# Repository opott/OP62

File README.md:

# OP62
This is a 60% (62 key) mechanical keyboard designed for Hackpad V2.

## PCB

## Case
The 3D printed case will consist of three parts:
- Top Assembly
- Plate
- Bottom Assembly

The top and bottom assembly will be attached with magnets. This is a screwless keyboard!

## Firmware
The current firmware is a **VERY** basic prototype created with [Pog](https://pog.heaper.de/).

A final firmware version will be created upon recieving the hardware.

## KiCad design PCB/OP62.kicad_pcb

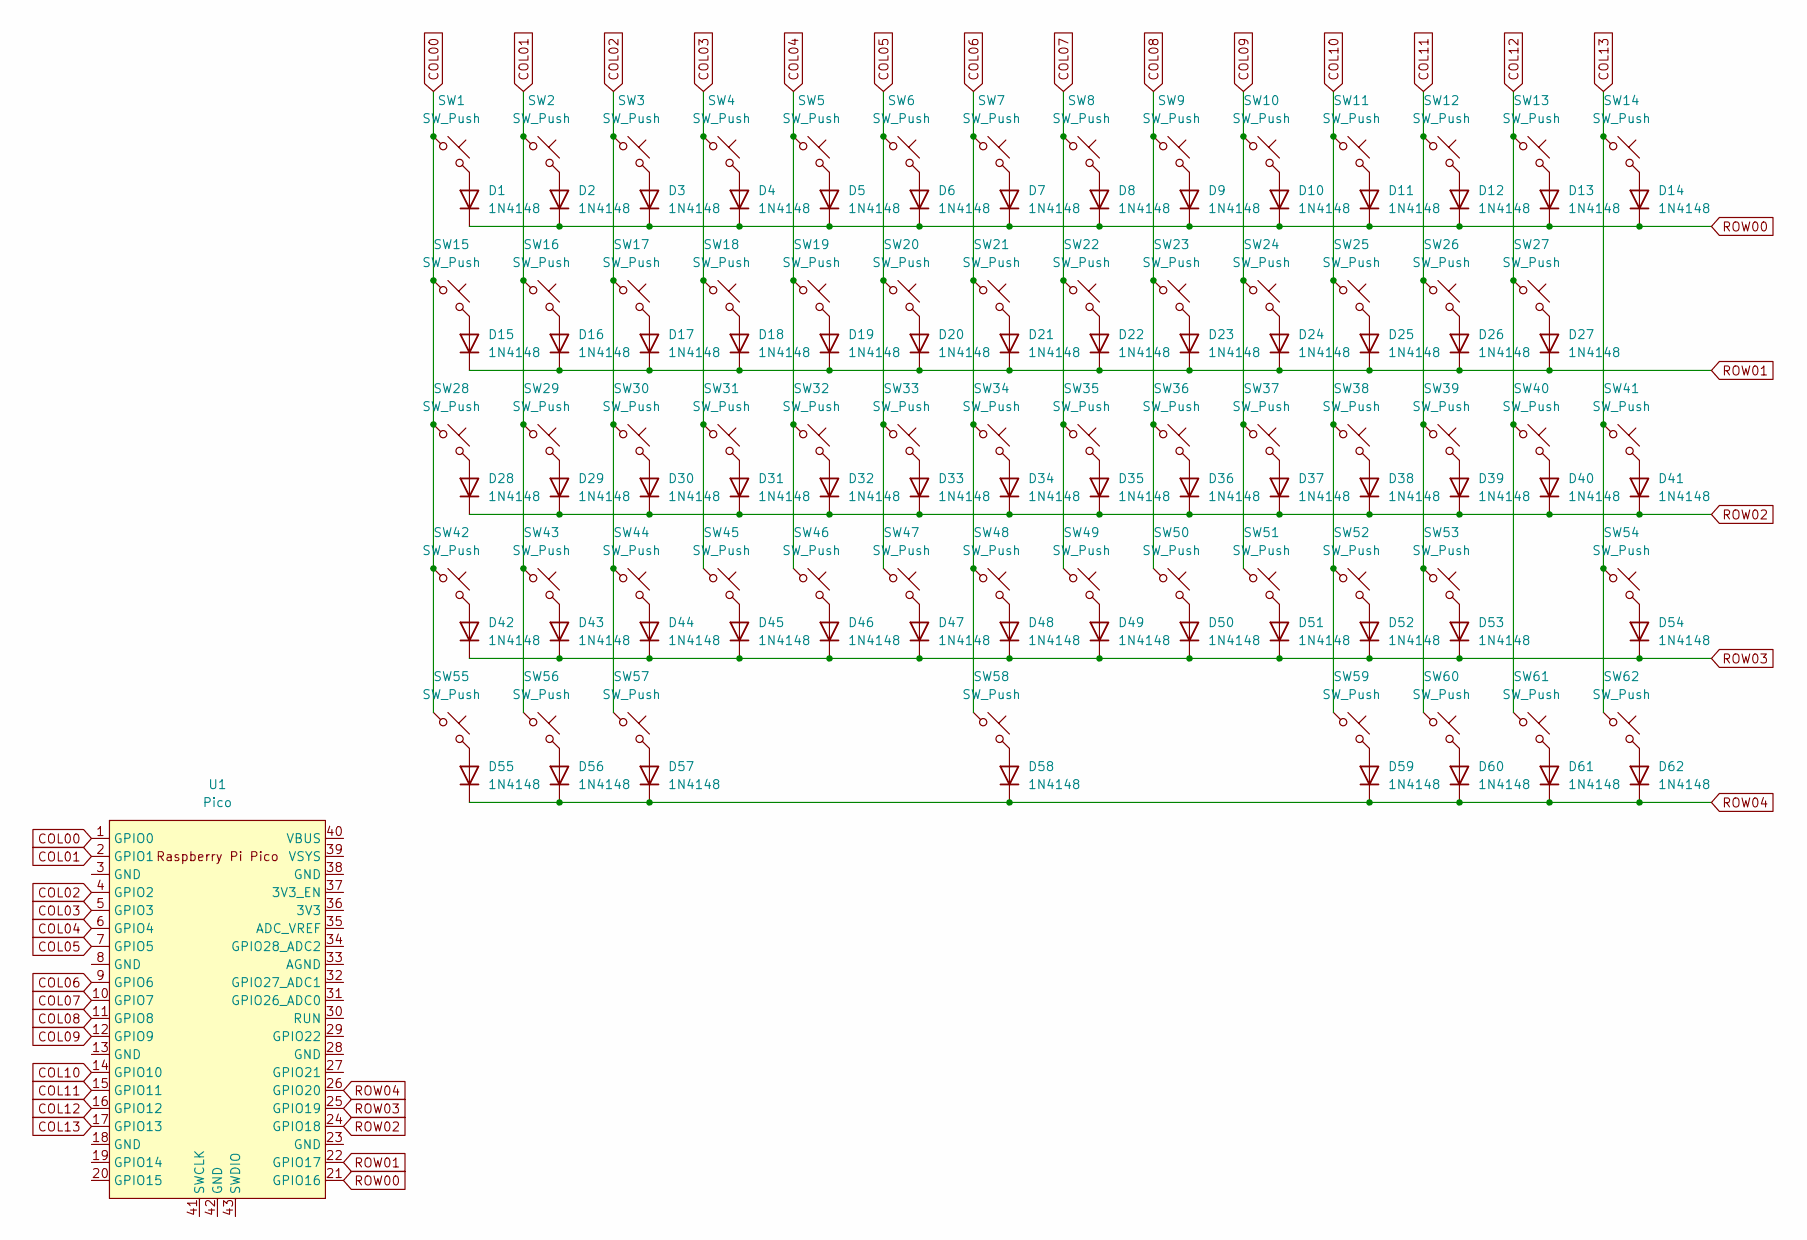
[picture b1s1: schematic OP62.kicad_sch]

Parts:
D1, D2, D3, D4, D5, D6, D7, D8, D9, D10, D11, D12, D13, D14, D15, D16, D17, D18, D19, D20, D21, D22, D23, D24, D25, D26, D27, D28, D29, D30, D31, D32, D33, D34, D35, D36, D37, D38, D39, D40, D41, D42, D43, D44, D45, D46, D47, D48, D49, D50, D51, D52, D53, D54, D55, D56, D57, D58, D59, D60, D61, D62: 1N4148; D_DO-35_SOD27_P7.62mm_Horizontal
SW1, SW2, SW3, SW4, SW5, SW6, SW7, SW8, SW9, SW10, SW11, SW12, SW13, SW16, SW17, SW18, SW19, SW20, SW21, SW22, SW23, SW24, SW25, SW26, SW27, SW29, SW30, SW31, SW32, SW33, SW34, SW35, SW36, SW37, SW38, SW39, SW40, SW43, SW44, SW45, SW46, SW47, SW48, SW49, SW50, SW51, SW52, SW53: SW_Push; MX-Alps-Hybrid-1U
SW14: SW_Push; MX-Alps-Hybrid-2U
SW15: SW_Push; MX-Alps-Hybrid-1.5U
SW28: SW_Push; MX-Alps-Hybrid-1.75U
SW41: SW_Push; MX-Alps-Hybrid-ISO
SW42, SW55, SW56, SW57, SW59, SW60, SW61, SW62: SW_Push; MX-Alps-Hybrid-1.25U
SW54: SW_Push; MX-Alps-Hybrid-2.75U
SW58: SW_Push; MX-Alps-Hybrid-6.25U
U1: Pico; RPi_Pico_SMD_TH

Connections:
COL00: SW1.1, SW15.1, SW28.1, SW42.1, SW55.1, U1.1 (GPIO0)
COL01: SW2.1, SW16.1, SW29.1, SW43.1, SW56.1, U1.2 (GPIO1)
COL02: SW3.1, SW17.1, SW30.1, SW44.1, SW57.1, U1.4 (GPIO2)
COL03: SW4.1, SW18.1, SW31.1, SW45.1, U1.5 (GPIO3)
COL04: SW5.1, SW19.1, SW32.1, SW46.1, U1.6 (GPIO4)
COL05: SW6.1, SW20.1, SW33.1, SW47.1, U1.7 (GPIO5)
COL06: SW7.1, SW21.1, SW34.1, SW48.1, SW58.1, U1.9 (GPIO6)
COL07: SW8.1, SW22.1, SW35.1, SW49.1, U1.10 (GPIO7)
COL08: SW9.1, SW23.1, SW36.1, SW50.1, U1.11 (GPIO8)
COL09: SW10.1, SW24.1, SW37.1, SW51.1, U1.12 (GPIO9)
COL10: SW11.1, SW25.1, SW38.1, SW52.1, SW59.1, U1.14 (GPIO10)
COL11: SW12.1, SW26.1, SW39.1, SW53.1, SW60.1, U1.15 (GPIO11)
COL12: SW13.1, SW27.1, SW40.1, SW61.1, U1.16 (GPIO12)
COL13: SW14.1, SW41.1, SW54.1, SW62.1, U1.17 (GPIO13)
unnamed: D1.2 (A), SW1.2
unnamed: D2.2 (A), SW2.2
unnamed: D3.2 (A), SW3.2
unnamed: D4.2 (A), SW4.2
unnamed: D5.2 (A), SW5.2
unnamed: D6.2 (A), SW6.2
unnamed: D7.2 (A), SW7.2
unnamed: D8.2 (A), SW8.2
unnamed: D9.2 (A), SW9.2
unnamed: D10.2 (A), SW10.2
unnamed: D11.2 (A), SW11.2
unnamed: D12.2 (A), SW12.2
unnamed: D13.2 (A), SW13.2
unnamed: D14.2 (A), SW14.2
unnamed: D15.2 (A), SW15.2
unnamed: D16.2 (A), SW16.2
unnamed: D17.2 (A), SW17.2
unnamed: D18.2 (A), SW18.2
unnamed: D19.2 (A), SW19.2
unnamed: D20.2 (A), SW20.2
unnamed: D21.2 (A), SW21.2
unnamed: D22.2 (A), SW22.2
unnamed: D23.2 (A), SW23.2
unnamed: D24.2 (A), SW24.2
unnamed: D25.2 (A), SW25.2
unnamed: D26.2 (A), SW26.2
unnamed: D27.2 (A), SW27.2
unnamed: D28.2 (A), SW28.2
unnamed: D29.2 (A), SW29.2
unnamed: D30.2 (A), SW30.2
unnamed: D31.2 (A), SW31.2
unnamed: D32.2 (A), SW32.2
unnamed: D33.2 (A), SW33.2
unnamed: D34.2 (A), SW34.2
unnamed: D35.2 (A), SW35.2
unnamed: D36.2 (A), SW36.2
unnamed: D37.2 (A), SW37.2
unnamed: D38.2 (A), SW38.2
unnamed: D39.2 (A), SW39.2
unnamed: D40.2 (A), SW40.2
unnamed: D41.2 (A), SW41.2
unnamed: D42.2 (A), SW42.2
unnamed: D43.2 (A), SW43.2
unnamed: D44.2 (A), SW44.2
unnamed: D45.2 (A), SW45.2
unnamed: D46.2 (A), SW46.2
unnamed: D47.2 (A), SW47.2
unnamed: D48.2 (A), SW48.2
unnamed: D49.2 (A), SW49.2
unnamed: D50.2 (A), SW50.2
unnamed: D51.2 (A), SW51.2
unnamed: D52.2 (A), SW52.2
unnamed: D53.2 (A), SW53.2
unnamed: D54.2 (A), SW54.2
unnamed: D55.2 (A), SW55.2
unnamed: D56.2 (A), SW56.2
unnamed: D57.2 (A), SW57.2
unnamed: D58.2 (A), SW58.2
unnamed: D59.2 (A), SW59.2
unnamed: D60.2 (A), SW60.2
unnamed: D61.2 (A), SW61.2
unnamed: D62.2 (A), SW62.2
ROW00: D1.1 (K), D2.1 (K), D3.1 (K), D4.1 (K), D5.1 (K), D6.1 (K), D7.1 (K), D8.1 (K), D9.1 (K), D10.1 (K), D11.1 (K), D12.1 (K), D13.1 (K), D14.1 (K), U1.21 (GPIO16)
ROW01: D15.1 (K), D16.1 (K), D17.1 (K), D18.1 (K), D19.1 (K), D20.1 (K), D21.1 (K), D22.1 (K), D23.1 (K), D24.1 (K), D25.1 (K), D26.1 (K), D27.1 (K), U1.22 (GPIO17)
ROW02: D28.1 (K), D29.1 (K), D30.1 (K), D31.1 (K), D32.1 (K), D33.1 (K), D34.1 (K), D35.1 (K), D36.1 (K), D37.1 (K), D38.1 (K), D39.1 (K), D40.1 (K), D41.1 (K), U1.24 (GPIO18)
ROW03: D42.1 (K), D43.1 (K), D44.1 (K), D45.1 (K), D46.1 (K), D47.1 (K), D48.1 (K), D49.1 (K), D50.1 (K), D51.1 (K), D52.1 (K), D53.1 (K), D54.1 (K), U1.25 (GPIO19)
ROW04: D55.1 (K), D56.1 (K), D57.1 (K), D58.1 (K), D59.1 (K), D60.1 (K), D61.1 (K), D62.1 (K), U1.26 (GPIO20)

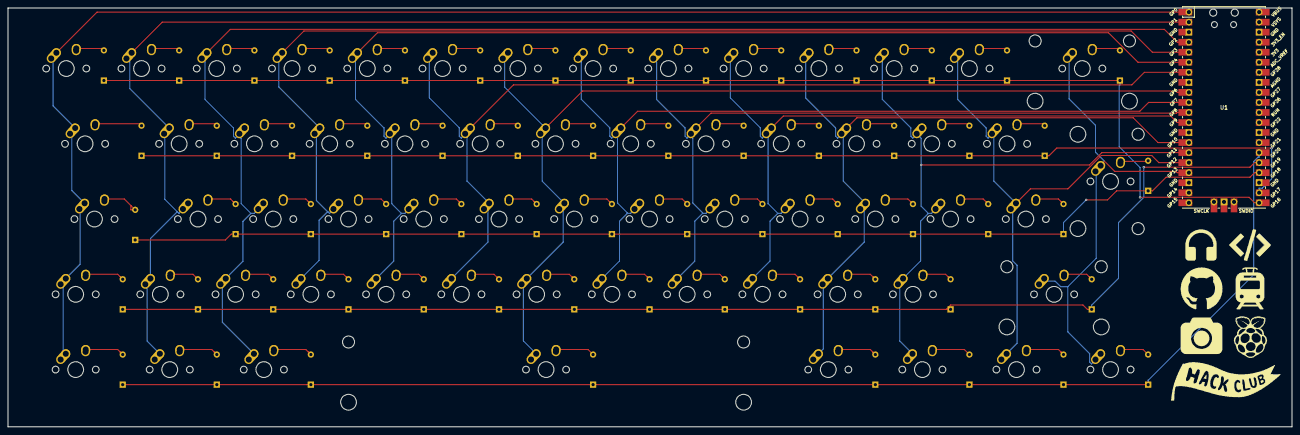
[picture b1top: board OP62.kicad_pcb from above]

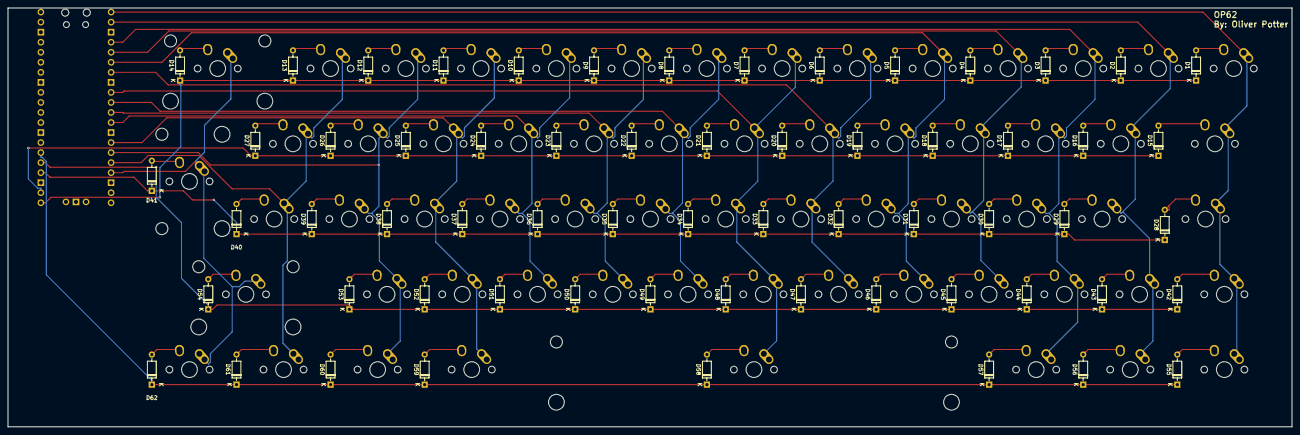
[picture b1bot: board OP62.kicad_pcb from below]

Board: 2 copper layers, 325.0 x 106.0 mm, 125 parts (62 on the bottom side), 81 nets.

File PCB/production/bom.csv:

Designator,Footprint,Quantity,Value,LCSC Part #
"D1, D10, D11, D12, D13, D14, D15, D16, D17, D18, D19, D2, D20, D21, D22, D23, D24, D25, D26, D27, D28, D29, D3, D30, D31, D32, D33, D34, D35, D36, D37, D38, D39, D4, D40, D41, D42, D43, D44, D45, D46, D47, D48, D49, D5, D50, D51, D52, D53, D54, D55, D56, D57, D58, D59, D6, D60, D61, D62, D7, D8, D9",D_DO-35_SOD27_P7.62mm_Horizontal,62,1N4148,
"SW1, SW10, SW11, SW12, SW13, SW16, SW17, SW18, SW19, SW2, SW20, SW21, SW22, SW23, SW24, SW25, SW26, SW27, SW29, SW3, SW30, SW31, SW32, SW33, SW34, SW35, SW36, SW37, SW38, SW39, SW4, SW40, SW43, SW44, SW45, SW46, SW47, SW48, SW49, SW5, SW50, SW51, SW52, SW53, SW6, SW7, SW8, SW9",MX-Alps-Hybrid-1U,48,SW_Push,
SW14,MX-Alps-Hybrid-2U,1,SW_Push,
SW15,MX-Alps-Hybrid-1.5U,1,SW_Push,
SW28,MX-Alps-Hybrid-1.75U,1,SW_Push,
SW41,MX-Alps-Hybrid-ISO,1,SW_Push,
"SW42, SW55, SW56, SW57, SW59, SW60, SW61, SW62",MX-Alps-Hybrid-1.25U,8,SW_Push,
SW54,MX-Alps-Hybrid-2.75U,1,SW_Push,
SW58,MX-Alps-Hybrid-6.25U,1,SW_Push,
U1,RPi_Pico_SMD_TH,1,Pico,
